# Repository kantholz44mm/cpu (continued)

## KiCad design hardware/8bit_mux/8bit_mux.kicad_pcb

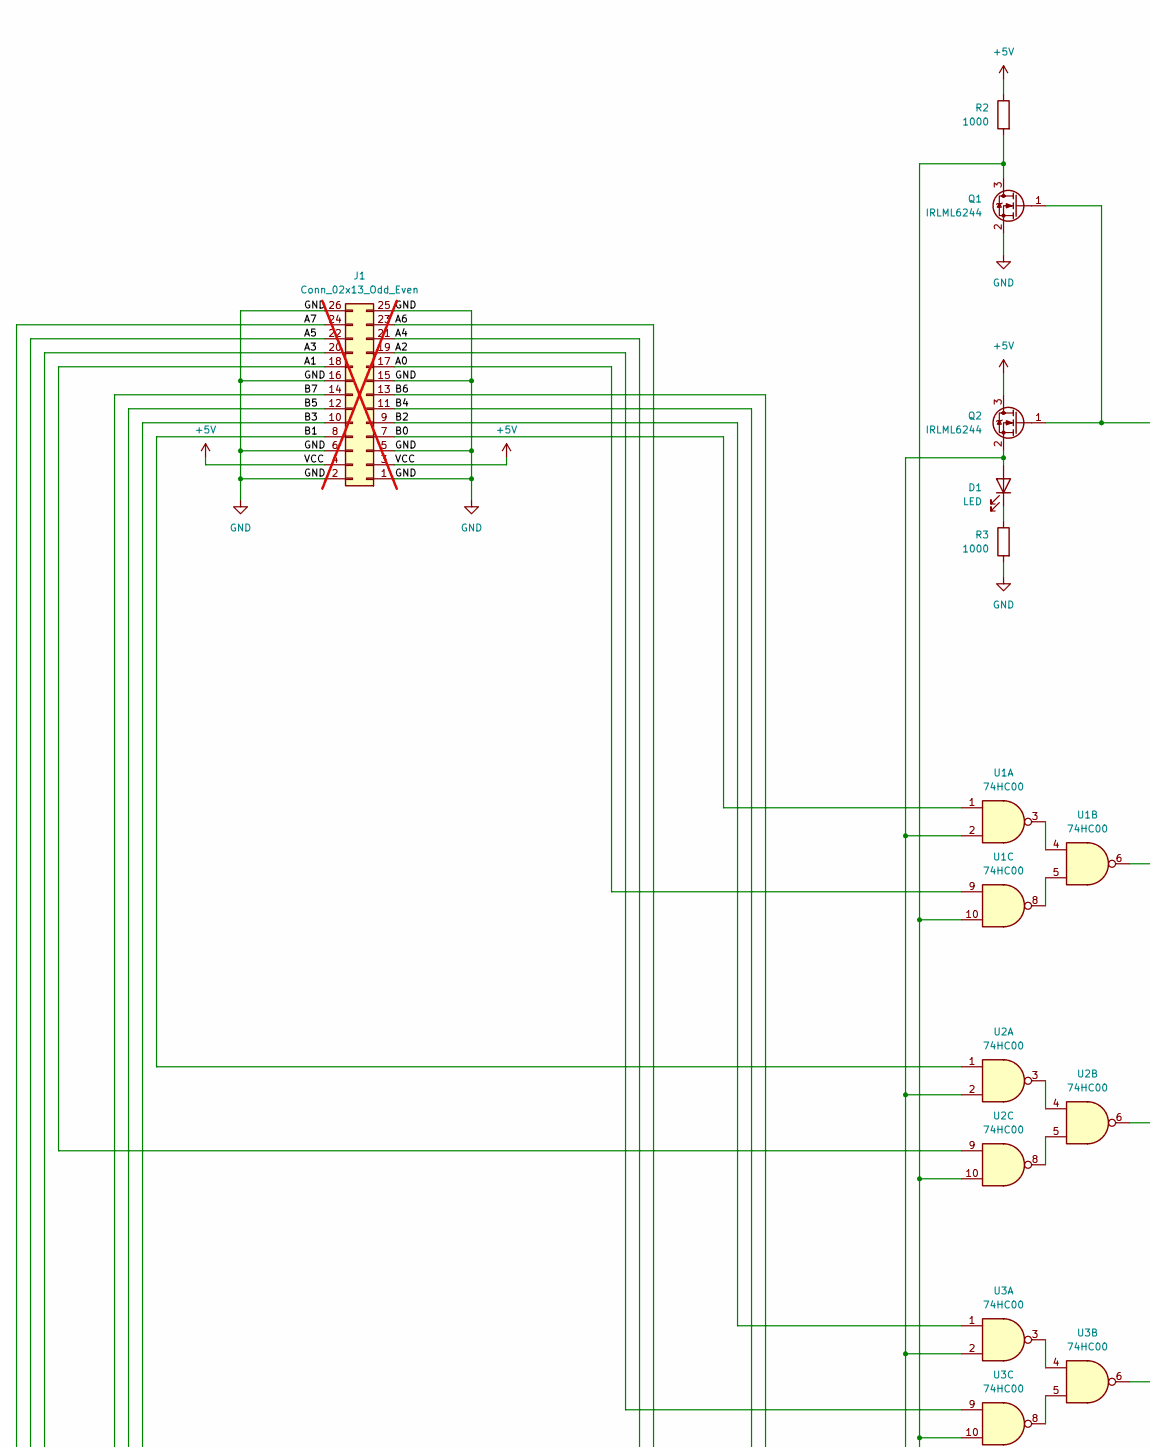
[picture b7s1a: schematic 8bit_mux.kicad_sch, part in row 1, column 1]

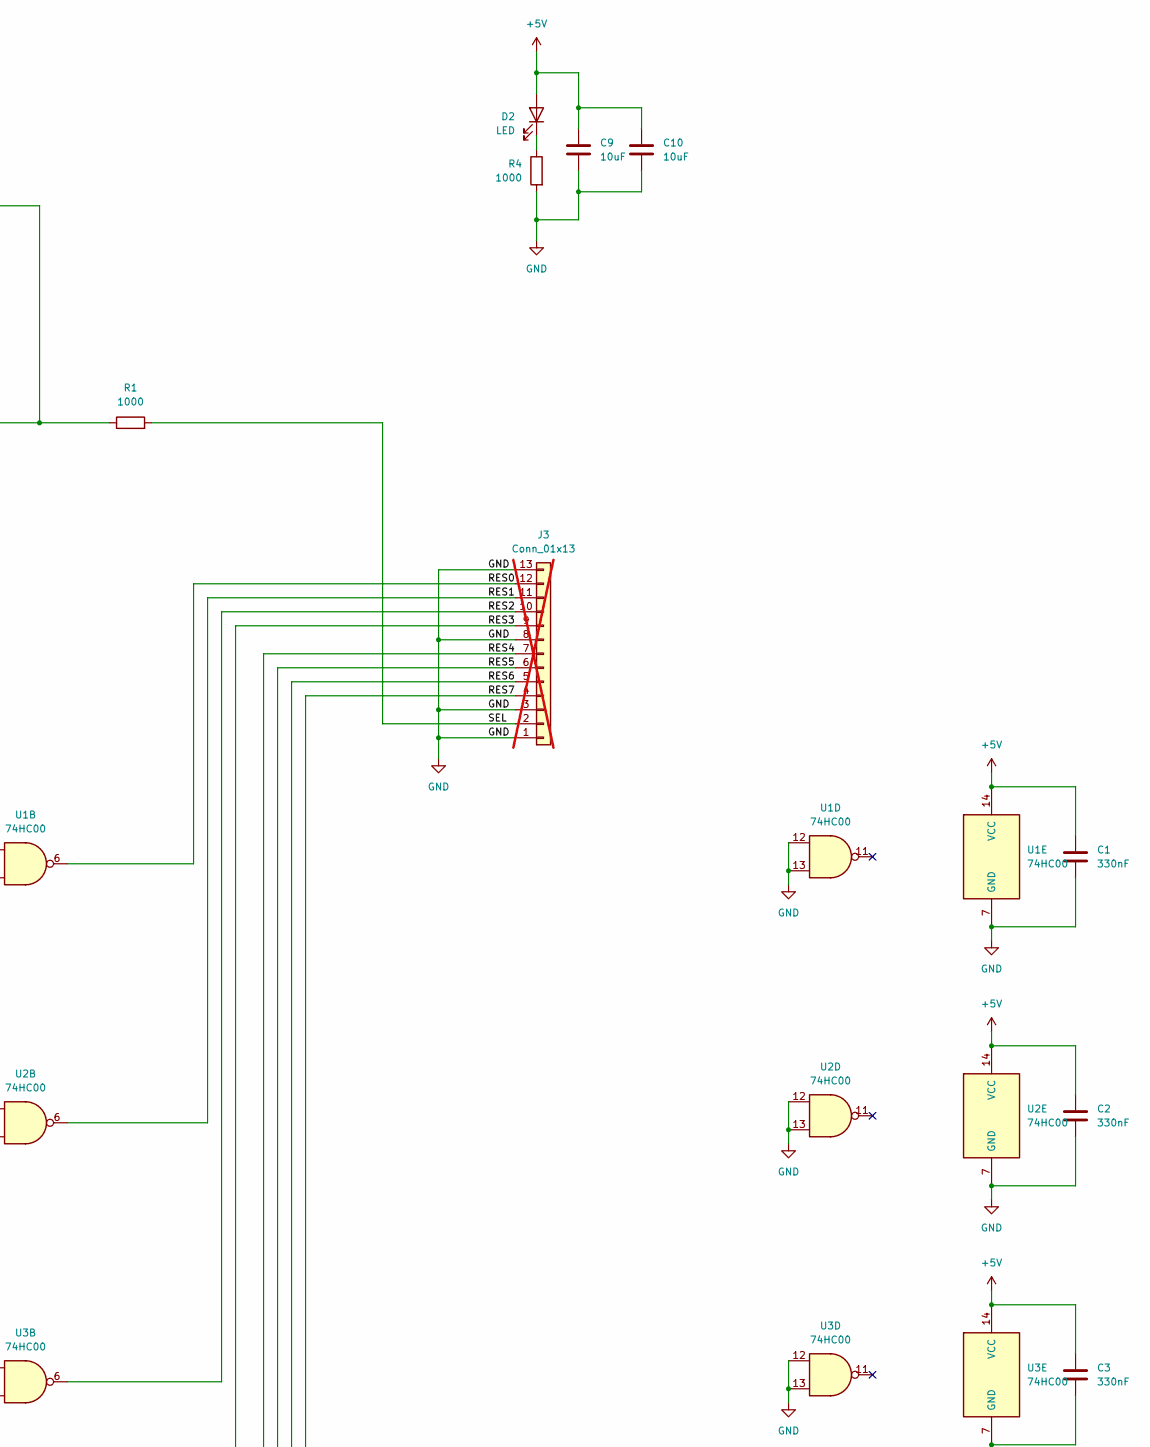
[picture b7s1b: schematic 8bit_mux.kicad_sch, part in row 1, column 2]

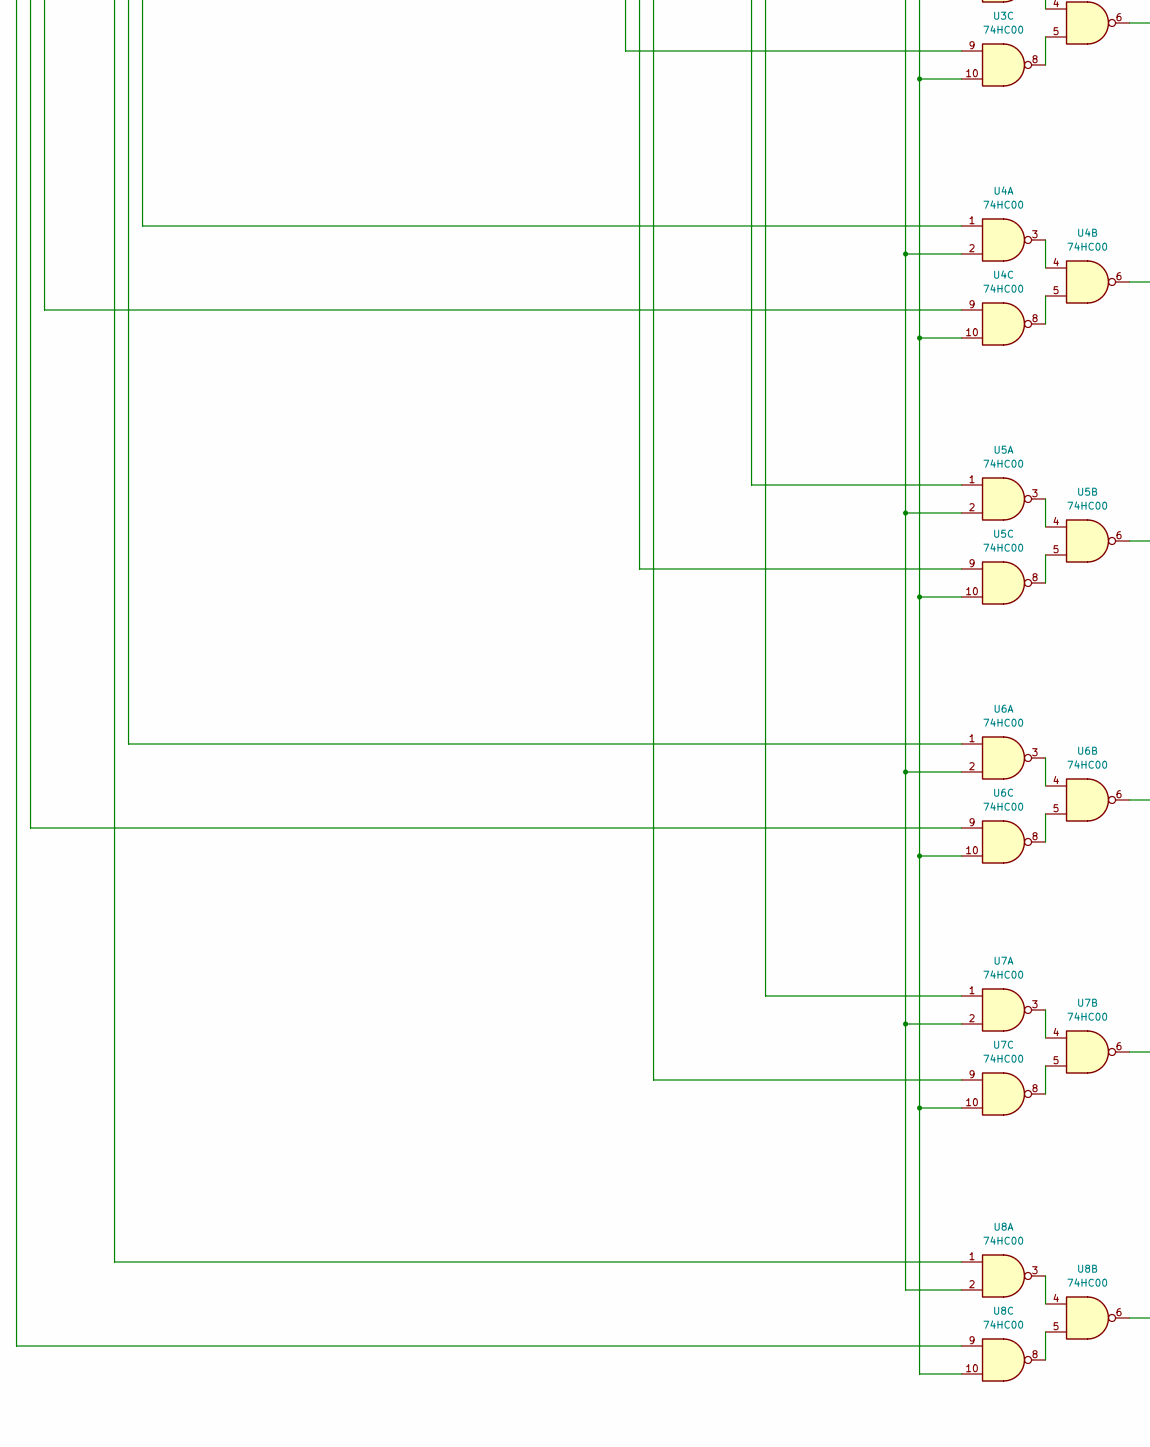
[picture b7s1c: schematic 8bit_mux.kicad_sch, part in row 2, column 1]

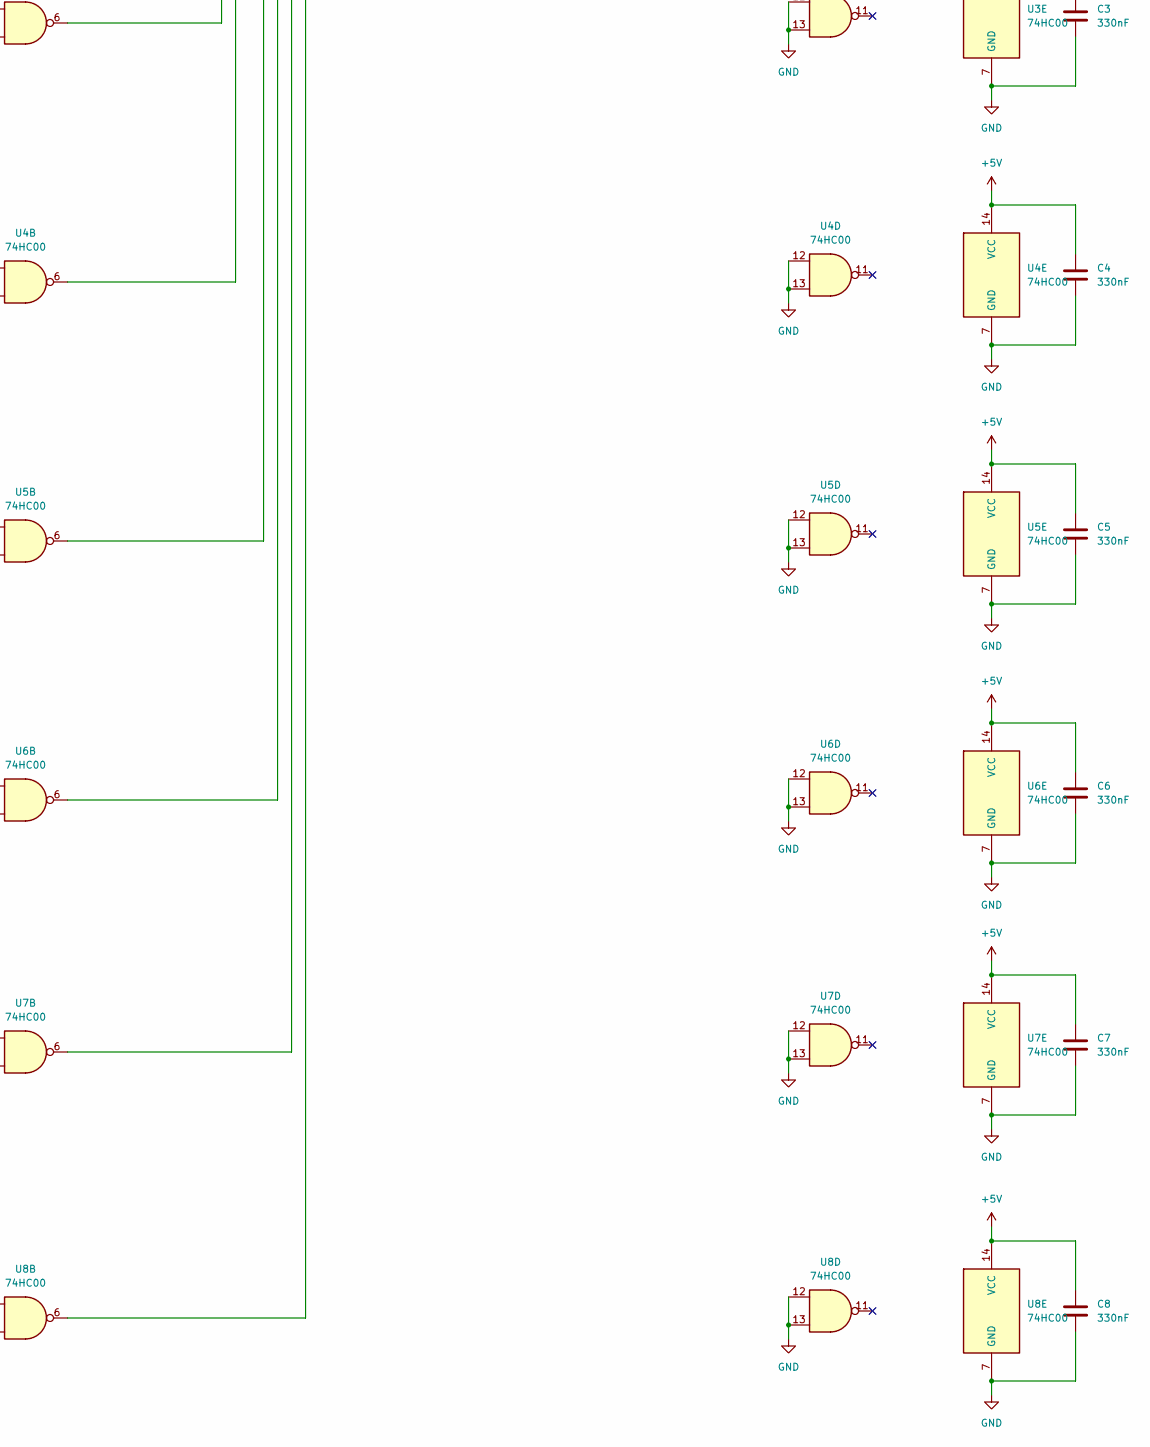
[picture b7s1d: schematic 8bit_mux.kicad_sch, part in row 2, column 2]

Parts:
C1, C2, C3, C4, C5, C6, C7, C8: 330nF; C_0603_1608Metric_Pad1.08x0.95mm_HandSolder; LCSC C2918485
C9, C10: 10uF; C_0603_1608Metric_Pad1.08x0.95mm_HandSolder; LCSC C2909630
D1, D2: LED; LED_0603_1608Metric_Pad1.05x0.95mm_HandSolder; LCSC C84267
J1: Conn_02x13_Odd_Even; PinHeader_2x13_P2.54mm_Vertical; not fitted
J3: Conn_01x13; PinHeader_1x13_P2.54mm_Vertical; not fitted
Q1, Q2: IRLML6244; SOT-23-3; LCSC C5123965
R1, R2, R3, R4: 1000; R_0603_1608Metric_Pad0.98x0.95mm_HandSolder; LCSC C21190
U1, U2, U3, U4, U5, U6, U7, U8: 74HC00; SOIC-14_3.9x8.7mm_P1.27mm; LCSC C5586

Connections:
+5V: C1.1, C2.1, C3.1, C4.1, C5.1, C6.1, C7.1, C8.1, C9.1, C10.1, D2.2 (A), J1.3, J1.4, Q2.3 (D), R2.1, U1.14 (VCC), U2.14 (VCC), U3.14 (VCC), U4.14 (VCC), U5.14 (VCC), U6.14 (VCC), U7.14 (VCC), U8.14 (VCC)
/A0: J1.17, U1.9
/A1: J1.18, U2.9
/A2: J1.19, U3.9
/A3: J1.20, U4.9
/A4: J1.21, U5.9
/A5: J1.22, U6.9
/A6: J1.23, U7.9
/A7: J1.24, U8.9
/B0: J1.7, U1.1
/B1: J1.8, U2.1
/B2: J1.9, U3.1
/B3: J1.10, U4.1
/B4: J1.11, U5.1
/B5: J1.12, U6.1
/B6: J1.13, U7.1
/B7: J1.14, U8.1
/RES0: J3.12, U1.6
/RES1: J3.11, U2.6
/RES2: J3.10, U3.6
/RES3: J3.9, U4.6
/RES4: J3.7, U5.6
/RES5: J3.6, U6.6
/RES6: J3.5, U7.6
/RES7: J3.4, U8.6
/SEL: J3.2, R1.2
GND: C1.2, C2.2, C3.2, C4.2, C5.2, C6.2, C7.2, C8.2, C9.2, C10.2, J1.1, J1.2, J1.5, J1.6, J1.15, J1.16, J1.25, J1.26, J3.1, J3.3, J3.8, J3.13, Q1.2 (S), R3.2, R4.2, U1.7 (GND), U1.12, U1.13, U2.7 (GND), U2.12, U2.13, U3.7 (GND), U3.12, U3.13, U4.7 (GND), U4.12, U4.13, U5.7 (GND), U5.12, U5.13, U6.7 (GND), U6.12, U6.13, U7.7 (GND), U7.12, U7.13, U8.7 (GND), U8.12, U8.13
unnamed: D1.2 (A), Q2.2 (S), U1.2, U2.2, U3.2, U4.2, U5.2, U6.2, U7.2, U8.2
unnamed: D1.1 (K), R3.1
unnamed: D2.1 (K), R4.1
unnamed: Q1.3 (D), R2.2, U1.10, U2.10, U3.10, U4.10, U5.10, U6.10, U7.10, U8.10
unnamed: Q1.1 (G), Q2.1 (G), R1.1
unnamed: U1.3, U1.4
unnamed: U1.5, U1.8
unnamed: U2.3, U2.4
unnamed: U2.5, U2.8
unnamed: U3.3, U3.4
unnamed: U3.5, U3.8
unnamed: U4.3, U4.4
unnamed: U4.5, U4.8
unnamed: U5.3, U5.4
unnamed: U5.5, U5.8
unnamed: U6.3, U6.4
unnamed: U6.5, U6.8
unnamed: U7.3, U7.4
unnamed: U7.5, U7.8
unnamed: U8.3, U8.4
unnamed: U8.5, U8.8

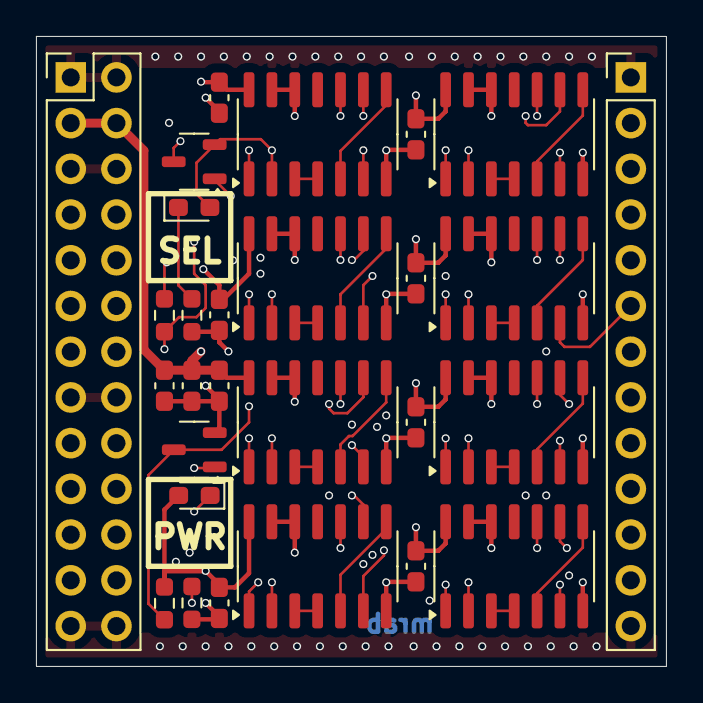
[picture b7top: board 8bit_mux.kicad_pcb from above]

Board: 4 copper layers, 35.0 x 35.0 mm, 28 parts (0 on the bottom side), 48 nets.

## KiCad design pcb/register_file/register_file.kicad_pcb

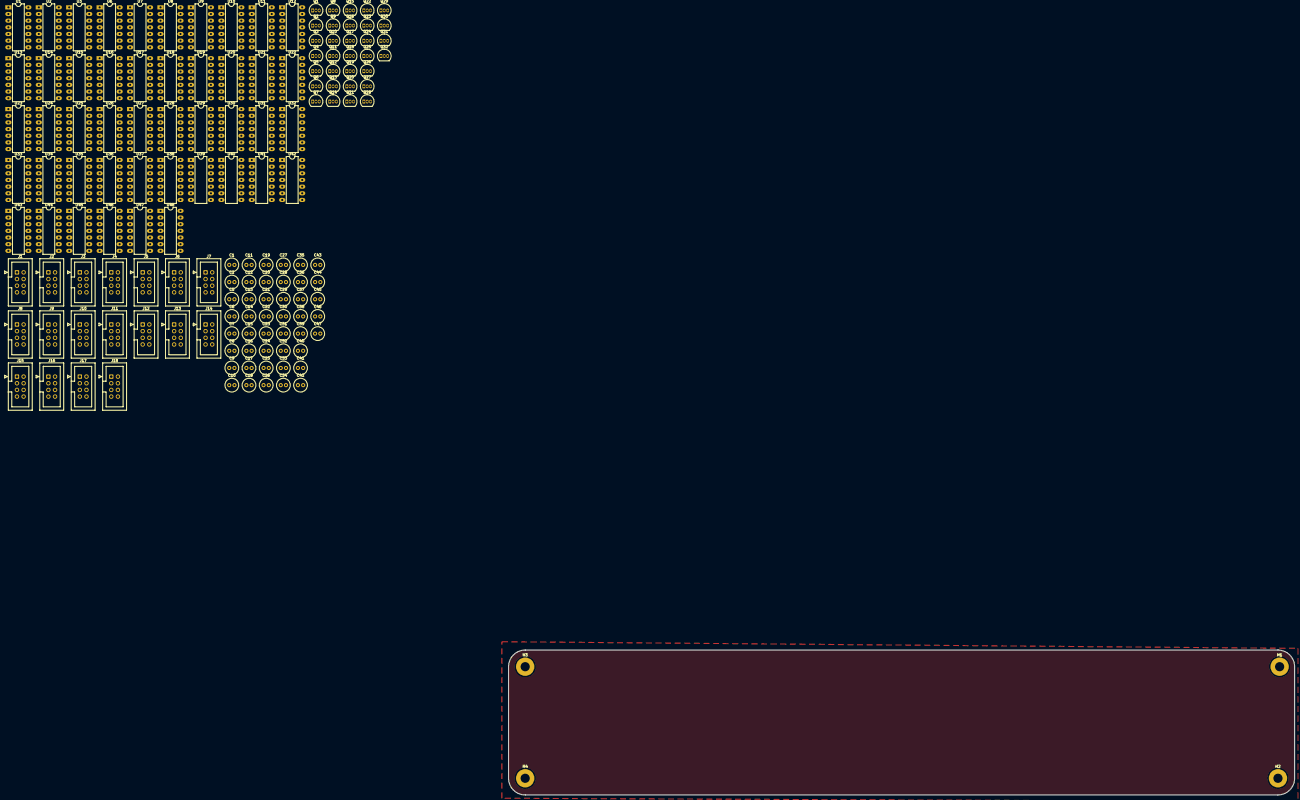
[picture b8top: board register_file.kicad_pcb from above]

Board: 2 copper layers, 299.7 x 55.2 mm, 145 parts (0 on the bottom side), 249 nets, no tracks yet.

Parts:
C1, C2, C5, C6, C7, C8, C9, C10, C11, C12, C13, C14, C15, C16, C17, C18, C19, C20, C21, C22, C23, C24, C25, C26, C27, C28, C29, C30, C31, C32, C33, C34, C35, C36, C37, C38, C39, C40, C41, C42, C43, C44, C45, C46, C47: C_Small; C_Radial_D5.0mm_H11.0mm_P2.00mm
H1, H2, H3, H4: MountingHole_Pad; MountingHole_3.5mm_Pad
J1: READ1; IDC-Header_2x04_P2.54mm_Vertical
J2: READ2; IDC-Header_2x04_P2.54mm_Vertical
J3: REG0_READ; IDC-Header_2x04_P2.54mm_Vertical
J4: WRITE; IDC-Header_2x04_P2.54mm_Vertical
J5: SELECT; IDC-Header_2x04_P2.54mm_Vertical
J6: CONTROL; IDC-Header_2x04_P2.54mm_Vertical
J7: REG0_CONTROL; IDC-Header_2x04_P2.54mm_Vertical
J8: REG1_CONTROL; IDC-Header_2x04_P2.54mm_Vertical
J9: REG2_CONTROL; IDC-Header_2x04_P2.54mm_Vertical
J10: REG3_CONTROL; IDC-Header_2x04_P2.54mm_Vertical
J11: REG0_WRITE; IDC-Header_2x04_P2.54mm_Vertical
J12: REG1_WRITE; IDC-Header_2x04_P2.54mm_Vertical
J13: REG2_WRITE; IDC-Header_2x04_P2.54mm_Vertical
J14: REG3_WRITE; IDC-Header_2x04_P2.54mm_Vertical
J15: REG1_READ; IDC-Header_2x04_P2.54mm_Vertical
J16: REG2_READ; IDC-Header_2x04_P2.54mm_Vertical
J17: REG3_READ; IDC-Header_2x04_P2.54mm_Vertical
J18: READP; IDC-Header_2x04_P2.54mm_Vertical
Q1, Q4, Q6, Q8, Q10, Q12, Q14, Q16, Q18, Q20, Q22, Q24, Q26, Q28, Q30, Q32: 2N7000; TO-92_Inline
Q2, Q3, Q5, Q7, Q9, Q11, Q13, Q15, Q17, Q19, Q21, Q23, Q25, Q27, Q29, Q31: BS250; TO-92_Inline
U1, U2, U3, U6, U7, U8, U9, U10, U11, U12, U13, U14, U15, U16, U17, U18, U19, U20, U21, U22, U23, U24, U25, U26, U27, U28, U29, U30, U31, U32, U33, U34, U35, U36, U37, U38, U39, U40, U41, U42, U43, U44, U45, U46, U47, U48: 74HC00; DIP-14_W7.62mm_LongPads

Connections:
+5V: C1.1, C2.1, C5.1, C6.1, C7.1, C8.1, C9.1, C10.1, C11.1, C12.1, C13.1, C14.1, C15.1, C16.1, C17.1, C18.1, C19.1, C20.1, C21.1, C22.1, C23.1, C24.1, C25.1, C26.1, C27.1, C28.1, C29.1, C30.1, C31.1, C32.1, C33.1, C34.1, C35.1, C36.1, C37.1, C38.1, C39.1, C40.1, C41.1, C42.1, C43.1, C44.1, C45.1, C46.1, C47.1, J6.7, J6.8, J7.7, J7.8, J8.7, J8.8, J9.7, J9.8, J10.7, J10.8, Q2.1 (D), Q3.1 (D), Q5.1 (D), Q7.1 (D), Q9.1 (D), Q11.1 (D), Q13.1 (D), Q15.1 (D), Q17.1 (D), Q19.1 (D), Q21.1 (D), Q23.1 (D), Q25.1 (D), Q27.1 (D), Q29.1 (D), Q31.1 (D), U1.14 (VCC), U2.14 (VCC), U3.14 (VCC), U6.14 (VCC), U7.14 (VCC), U8.14 (VCC), U9.14 (VCC), U10.14 (VCC), U11.14 (VCC), U12.14 (VCC), U13.14 (VCC), U14.14 (VCC), U15.14 (VCC), U16.14 (VCC), U17.14 (VCC), U18.14 (VCC), U19.14 (VCC), U20.14 (VCC), U21.14 (VCC), U22.14 (VCC), U23.14 (VCC), U24.14 (VCC), U25.14 (VCC), U26.14 (VCC), U27.14 (VCC), U28.14 (VCC), U29.14 (VCC), U30.14 (VCC), U31.14 (VCC), U32.14 (VCC), U33.14 (VCC), U34.14 (VCC), U35.14 (VCC), U36.14 (VCC), U37.14 (VCC), U38.14 (VCC), U39.14 (VCC), U40.14 (VCC), U41.14 (VCC), U42.14 (VCC), U43.14 (VCC), U44.14 (VCC), U45.14 (VCC), U46.14 (VCC), U47.14 (VCC), U48.14 (VCC)
GND: C1.2, C2.2, C5.2, C6.2, C7.2, C8.2, C9.2, C10.2, C11.2, C12.2, C13.2, C14.2, C15.2, C16.2, C17.2, C18.2, C19.2, C20.2, C21.2, C22.2, C23.2, C24.2, C25.2, C26.2, C27.2, C28.2, C29.2, C30.2, C31.2, C32.2, C33.2, C34.2, C35.2, C36.2, C37.2, C38.2, C39.2, C40.2, C41.2, C42.2, C43.2, C44.2, C45.2, C46.2, C47.2, H1.1, H2.1, H3.1, H4.1, J5.3, J5.6, J6.4, J6.5, J6.6, J7.4, J7.5, J7.6, J8.4, J8.5, J8.6, J9.4, J9.5, J9.6, J10.4, J10.5, J10.6, Q1.1 (S), Q4.1 (S), Q6.1 (S), Q8.1 (S), Q10.1 (S), Q12.1 (S), Q14.1 (S), Q16.1 (S), Q18.1 (S), Q20.1 (S), Q22.1 (S), Q24.1 (S), Q26.1 (S), Q28.1 (S), Q30.1 (S), Q32.1 (S), U1.7 (GND), U2.7 (GND), U3.7 (GND), U6.7 (GND), U7.7 (GND), U8.7 (GND), U9.7 (GND), U10.7 (GND), U11.7 (GND), U12.7 (GND), U13.7 (GND), U14.7 (GND), U15.7 (GND), U16.7 (GND), U17.7 (GND), U18.7 (GND), U19.7 (GND), U20.7 (GND), U21.7 (GND), U22.7 (GND), U23.7 (GND), U24.7 (GND), U25.7 (GND), U26.7 (GND), U27.7 (GND), U28.7 (GND), U29.7 (GND), U30.7 (GND), U31.7 (GND), U32.7 (GND), U33.7 (GND), U34.7 (GND), U35.7 (GND), U36.7 (GND), U37.7 (GND), U38.7 (GND), U39.7 (GND), U40.7 (GND), U41.7 (GND), U42.7 (GND), U43.7 (GND), U44.7 (GND), U45.7 (GND), U46.7 (GND), U47.7 (GND), U48.7 (GND)
unnamed: J1.1, U19.3
unnamed: J1.2, U19.8
unnamed: J1.3, U21.3
unnamed: J1.4, U21.8
unnamed: J1.5, U30.3
unnamed: J1.6, U30.8
unnamed: J1.7, U39.3
unnamed: J1.8, U39.8
unnamed: J2.1, U19.6
unnamed: J2.2, U19.11
unnamed: J2.3, U21.6
unnamed: J2.4, U21.11
unnamed: J2.5, U30.6
unnamed: J2.6, U30.11
unnamed: J2.7, U39.6
unnamed: J2.8, U39.11
unnamed: J3.1, U11.2, U13.2
unnamed: J3.2, U15.2, U17.2
unnamed: J3.3, U20.2, U23.2
unnamed: J3.4, U25.2, U27.2
unnamed: J3.5, U29.2, U32.2
unnamed: J3.6, U34.2, U36.2
unnamed: J3.7, U38.2, U41.2
unnamed: J3.8, U43.2, U45.2
unnamed: J4.1, U48.12, U48.13
unnamed: J4.2, U48.9, U48.10
unnamed: J4.3, U48.4, U48.5
unnamed: J4.4, U48.1, U48.2
unnamed: J4.5, U47.12, U47.13
unnamed: J4.6, U47.9, U47.10
unnamed: J4.7, U47.4, U47.5
unnamed: J4.8, U47.1, U47.2
unnamed: J5.1, U6.1, U6.2, U8.2, U8.10
unnamed: J5.2, U6.4, U6.5, U7.9, U8.9
unnamed: J5.4, U2.10, U2.13, U3.9, U3.10
unnamed: J5.5, U2.4, U2.12, U3.12, U3.13
unnamed: J5.7, U1.10, U1.13, U3.1, U3.2
unnamed: J5.8, U1.4, U1.12, U3.4, U3.5
unnamed: J6.2, U9.1, U9.9, U10.1, U10.9
unnamed: J7.2, U9.6
unnamed: J8.2, U9.11
unnamed: J9.2, U10.6
unnamed: J6.1, J7.1, J8.1, J9.1, J10.1
unnamed: J10.2, U10.11
unnamed: J6.3, J7.3, J8.3, J9.3, J10.3
unnamed: J11.1, J12.1, J13.1, J14.1, Q15.3 (S), Q16.3 (D)
unnamed: J11.2, J12.2, J13.2, J14.2, Q13.3 (S), Q14.3 (D)
unnamed: J11.3, J12.3, J13.3, J14.3, Q11.3 (S), Q12.3 (D)
unnamed: J11.4, J12.4, J13.4, J14.4, Q9.3 (S), Q10.3 (D)
unnamed: J11.5, J12.5, J13.5, J14.5, Q7.3 (S), Q8.3 (D)
unnamed: J11.6, J12.6, J13.6, J14.6, Q5.3 (S), Q6.3 (D)
unnamed: J11.7, J12.7, J13.7, J14.7, Q3.3 (S), Q4.3 (D)
unnamed: J11.8, J12.8, J13.8, J14.8, Q1.3 (D), Q2.3 (S)
unnamed: J15.1, U11.5, U13.5
unnamed: J15.2, U15.5, U17.5
unnamed: J15.3, U20.5, U23.5
unnamed: J15.4, U25.5, U27.5
unnamed: J15.5, U29.5, U32.5
unnamed: J15.6, U34.5, U36.5
unnamed: J15.7, U38.5, U41.5
unnamed: J15.8, U43.5, U45.5
unnamed: J16.1, U12.2, U14.2
unnamed: J16.2, U16.2, U18.2
unnamed: J16.3, U22.2, U24.2
unnamed: J16.4, U26.2, U28.2
unnamed: J16.5, U31.2, U33.2
unnamed: J16.6, U35.2, U37.2
unnamed: J16.7, U40.2, U42.2
unnamed: J16.8, U44.2, U46.2
unnamed: J17.1, J18.1, U12.5, U14.5
unnamed: J17.2, J18.2, U16.5, U18.5
unnamed: J17.3, J18.3, U22.5, U24.5
unnamed: J17.4, J18.4, U26.5, U28.5
unnamed: J17.5, J18.5, U31.5, U33.5
unnamed: J17.6, J18.6, U35.5, U37.5
unnamed: J17.7, J18.7, U40.5, U42.5
unnamed: J17.8, J18.8, U44.5, U46.5
unnamed: Q1.2 (G), Q2.2 (G), U47.3
unnamed: Q3.2 (G), Q4.2 (G), U47.6
unnamed: Q5.2 (G), Q6.2 (G), U47.8
unnamed: Q7.2 (G), Q8.2 (G), U47.11
unnamed: Q9.2 (G), Q10.2 (G), U48.3
unnamed: Q11.2 (G), Q12.2 (G), U48.6
unnamed: Q13.2 (G), Q14.2 (G), U48.8
unnamed: Q15.2 (G), Q16.2 (G), U48.11
unnamed: Q17.2 (G), Q18.2 (G), U1.3
unnamed: Q17.3 (S), Q18.3 (D), U11.1, U15.1, U20.1, U25.1, U29.1, U34.1, U38.1, U43.1
unnamed: Q19.2 (G), Q20.2 (G), U1.6
unnamed: Q19.3 (S), Q20.3 (D), U11.4, U15.4, U20.4, U25.4, U29.4, U34.4, U38.4, U43.4
unnamed: Q21.2 (G), Q22.2 (G), U1.8
unnamed: Q21.3 (S), Q22.3 (D), U12.1, U16.1, U22.1, U26.1, U31.1, U35.1, U40.1, U44.1
unnamed: Q23.2 (G), Q24.2 (G), U1.11
unnamed: Q23.3 (S), Q24.3 (D), U12.4, U16.4, U22.4, U26.4, U31.4, U35.4, U40.4, U44.4
unnamed: Q25.2 (G), Q26.2 (G), U2.3
unnamed: Q25.3 (S), Q26.3 (D), U14.4, U18.4, U24.4, U28.4, U33.4, U37.4, U42.4, U46.4
unnamed: Q27.2 (G), Q28.2 (G), U2.6
unnamed: Q27.3 (S), Q28.3 (D), U14.1, U18.1, U24.1, U28.1, U33.1, U37.1, U42.1, U46.1
unnamed: Q29.2 (G), Q30.2 (G), U2.8
unnamed: Q29.3 (S), Q30.3 (D), U13.4, U17.4, U23.4, U27.4, U32.4, U36.4, U41.4, U45.4
unnamed: Q31.2 (G), Q32.2 (G), U2.11
unnamed: Q31.3 (S), Q32.3 (D), U13.1, U17.1, U23.1, U27.1, U32.1, U36.1, U41.1, U45.1
unnamed: U1.1, U1.9, U3.6
unnamed: U1.2, U1.5, U3.3
unnamed: U2.1, U2.9, U3.11
unnamed: U2.2, U2.5, U3.8
unnamed: U6.3, U7.2, U7.10
unnamed: U6.6, U7.1, U8.1
unnamed: U7.3, U7.4, U7.5
unnamed: U7.6, U9.2
unnamed: U7.11, U9.10
unnamed: U7.8, U7.12, U7.13
unnamed: U8.3, U8.4, U8.5
unnamed: U8.8, U8.12, U8.13
unnamed: U9.3, U9.4, U9.5
unnamed: U9.8, U9.12, U9.13
unnamed: U8.6, U10.2
unnamed: U10.3, U10.4, U10.5
unnamed: U8.11, U10.10
unnamed: U10.8, U10.12, U10.13
unnamed: U11.3, U11.9
unnamed: U11.6, U11.10
unnamed: U11.11, U19.1
unnamed: U11.8, U11.12, U11.13
unnamed: U12.3, U12.9
unnamed: U12.6, U12.10
unnamed: U12.11, U19.2
unnamed: U12.8, U12.12, U12.13
unnamed: U13.3, U13.9
unnamed: U13.6, U13.10
unnamed: U13.11, U19.4
unnamed: U13.8, U13.12, U13.13
unnamed: U14.3, U14.9
unnamed: U14.6, U14.10
unnamed: U14.11, U19.5
unnamed: U14.8, U14.12, U14.13
unnamed: U15.3, U15.9
unnamed: U15.6, U15.10
unnamed: U15.11, U19.9
unnamed: U15.8, U15.12, U15.13
unnamed: U16.3, U16.9
unnamed: U16.6, U16.10
unnamed: U16.11, U19.10
unnamed: U16.8, U16.12, U16.13
unnamed: U17.3, U17.9
unnamed: U17.6, U17.10
unnamed: U17.11, U19.12
unnamed: U17.8, U17.12, U17.13
unnamed: U18.3, U18.9
unnamed: U18.6, U18.10
unnamed: U18.11, U19.13
unnamed: U18.8, U18.12, U18.13
unnamed: U20.3, U20.9
unnamed: U20.6, U20.10
unnamed: U20.11, U21.1
unnamed: U20.8, U20.12, U20.13
unnamed: U21.2, U22.11
unnamed: U21.4, U23.11
unnamed: U21.5, U24.11
unnamed: U21.9, U25.11
unnamed: U21.10, U26.11
unnamed: U21.12, U27.11
unnamed: U21.13, U28.11
unnamed: U22.3, U22.9
unnamed: U22.6, U22.10
unnamed: U22.8, U22.12, U22.13
unnamed: U23.3, U23.9
unnamed: U23.6, U23.10
unnamed: U23.8, U23.12, U23.13
unnamed: U24.3, U24.9
unnamed: U24.6, U24.10
unnamed: U24.8, U24.12, U24.13
unnamed: U25.3, U25.9
unnamed: U25.6, U25.10
unnamed: U25.8, U25.12, U25.13
unnamed: U26.3, U26.9
unnamed: U26.6, U26.10
unnamed: U26.8, U26.12, U26.13
unnamed: U27.3, U27.9
unnamed: U27.6, U27.10
unnamed: U27.8, U27.12, U27.13
unnamed: U28.3, U28.9
unnamed: U28.6, U28.10
unnamed: U28.8, U28.12, U28.13
unnamed: U29.3, U29.9
unnamed: U29.6, U29.10
unnamed: U29.11, U30.1
unnamed: U29.8, U29.12, U29.13
unnamed: U30.2, U31.11
unnamed: U30.4, U32.11
unnamed: U30.5, U33.11
unnamed: U30.9, U34.11
unnamed: U30.10, U35.11
unnamed: U30.12, U36.11
unnamed: U30.13, U37.11
unnamed: U31.3, U31.9
unnamed: U31.6, U31.10
unnamed: U31.8, U31.12, U31.13
unnamed: U32.3, U32.9
unnamed: U32.6, U32.10
unnamed: U32.8, U32.12, U32.13
unnamed: U33.3, U33.9
unnamed: U33.6, U33.10
unnamed: U33.8, U33.12, U33.13
unnamed: U34.3, U34.9
unnamed: U34.6, U34.10
unnamed: U34.8, U34.12, U34.13
unnamed: U35.3, U35.9
unnamed: U35.6, U35.10
unnamed: U35.8, U35.12, U35.13
unnamed: U36.3, U36.9
unnamed: U36.6, U36.10
unnamed: U36.8, U36.12, U36.13
unnamed: U37.3, U37.9
unnamed: U37.6, U37.10
unnamed: U37.8, U37.12, U37.13
unnamed: U38.3, U38.9
unnamed: U38.6, U38.10
unnamed: U38.11, U39.1
unnamed: U38.8, U38.12, U38.13
unnamed: U39.2, U40.11
unnamed: U39.4, U41.11
unnamed: U39.5, U42.11
unnamed: U39.9, U43.11
unnamed: U39.10, U44.11
unnamed: U39.12, U45.11
unnamed: U39.13, U46.11
unnamed: U40.3, U40.9
unnamed: U40.6, U40.10
unnamed: U40.8, U40.12, U40.13
unnamed: U41.3, U41.9
unnamed: U41.6, U41.10
unnamed: U41.8, U41.12, U41.13
unnamed: U42.3, U42.9
unnamed: U42.6, U42.10
unnamed: U42.8, U42.12, U42.13
unnamed: U43.3, U43.9
unnamed: U43.6, U43.10
unnamed: U43.8, U43.12, U43.13
unnamed: U44.3, U44.9
unnamed: U44.6, U44.10
unnamed: U44.8, U44.12, U44.13
unnamed: U45.3, U45.9
unnamed: U45.6, U45.10
unnamed: U45.8, U45.12, U45.13
unnamed: U46.3, U46.9
unnamed: U46.6, U46.10
unnamed: U46.8, U46.12, U46.13

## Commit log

2023-11-19 Initial state
2023-11-20 started work on assembler
2023-11-20 sim standing, MWI, ADD working
2023-11-20 assembler: encoding done, mostly untested as of yet
2023-11-20 added test case
2023-11-20 added .gitignore
2023-11-20 removed build files
2023-11-20 moved gitignore and cleaned up
2023-11-21 parsing tokens
2023-11-21 parsing first couple instructions
2023-11-21 all mnemonics can be assembled
2023-11-23 compiling and executing the first program
2023-11-25 reverted to 4 register core
2023-11-25 changed to async SRAM, added IO bus
2023-11-25 added example GPIO output, working fibonacci program
2023-11-25 removed example gpio setup
2023-11-26 16 bit fibonacci working
2023-11-30 Asynchronous reset lines for all registers
2023-11-30 added logic for halt/continue and HCF instruction
2023-11-30 Added Async CLR to flags register
2023-11-30 consolidated
2023-12-21 added kicad files for register
2024-01-16 register file
2024-04-20 separate page register
2024-04-21 label support for assembler
2024-04-21 comma = whitespace in assembler
2024-04-24 Fixed B Operand flag for ALUI and CMPI
2024-04-24 ALUF and ALUFI
2024-04-24 fixed Memory clocking
2024-10-23 clean up repo
2024-10-24 added project documentation documents
2024-11-07 feedback
2024-11-07 updated ISA spec
2024-11-07 added framework for thesis
2024-11-07 added interconnect & layout diagram
2024-11-23 Removed JZ and JNZ, made BZ and BNZ take RO2 as decider
2024-11-24 added register pcb
2024-11-24 started CPU emulator software
2024-11-24 added emulator tick logic, only ALU missing
2024-11-25 added ALU from combinatorial emulation
2024-11-25 fixed order of ALU flags
2024-11-26 fixed overflow flag checking in fib example
2024-11-26 added simple graphics test, drawing rectangle
2024-11-26 fixed unused imports, added 'current address' ($) to assembler
2024-11-26 added example for function calling
2024-12-04 redesigned register PCB with SMD components
2024-12-05 generated production files, including BOM and POS
2024-12-05 removed redundant mux from ALU
2024-12-05 added section on ISA design
2024-12-08 redesigned register using SMD components
2024-12-10 Added schematic for alu sub/add module
2024-12-11 layout done for alu add sub (missing test points)
2024-12-11 finalized PCB for ordering (LCSC parts, silkscreen, etc)
2025-01-19 worked some on the thesis, started next alu module
2025-01-19 WIP, moved all control signals into OPROM, modified assembler as such
2025-01-19 added johnson 4 bit counter for synchronisation (fixes branching)
2025-01-21 finished design of ALU binary logic module
2025-01-21 added initial schematic for ALU shifter module
2025-01-22 added section on commissioning
2025-01-22 added LED indicators for ALU shift module
2025-01-23 added section on timing, restructured
2025-01-25 added 8 bit mux pcb, started work on ALU shifter
2025-01-28 finished ALU Shift module, all ALU modules completed
2025-01-31 added math expression evaluator to assembler, updated emulator
2025-02-04 started work on ALU motherboard
2025-02-04 fixed schematic of ALU motherboard
2025-02-05 finished schematic and draft of ALU motherboard
2025-02-09 feedback to ALU motherboard PCB
2025-02-09 more ALU motherboard feedback
2025-02-11 reverted changes to alu_shift
2025-02-11 added PWR indicator to alu_shift
2025-02-12 fixed mux include
2025-02-12 ALU shifter, bitops and motherboard as ordered
2025-02-17 removed regex dependency from lexer
2025-02-17 reduced dependencies
2025-03-13 updated boolean logic section
2025-03-14 updated section on boolean logic and cpu and timing
2025-03-16 added sections on design, reworked isa section
2025-03-19 added section on software
2025-03-19 finished PCB assembly layout
2025-03-20 started section on software emulator
2025-03-20 added single-pcb ALU V2
2025-03-23 WIP progress on ALU V2 pcb
2025-03-24 more WIP work on ALU V2
2025-03-25 further WIP on ALU V2 pcb
2025-03-25 ALU V2 done?
2025-03-26 small fixes in ALU V2, started work on register fabric, schematic done (?)
2025-04-01 fixed ALU order of Op bits, finished register fabric schematic
2025-04-01 started work on register fabric PCB layout, grouped LEDs
2025-04-02 finished Rev A of register fabric pcb
2025-04-03 added fiducials and markers to ALU, started on register fabric
2025-04-04 added fiducials to register fabric REV A
2025-04-06 small fixes on register fabric
2025-04-08 did a good chunk of IO PCB schematic
2025-04-15 IO PCB schematic REV A done?
2025-04-16 added folder for documentation organisation
2025-04-16 Added sections on microcode and busses
2025-04-17 added section on microcode
2025-04-19 almost done with placement for IO board
2025-04-21 finished IO PCB placement
2025-04-21 large chunk of IO PCB routing is done
2025-04-22 more work on IO PCB routing
2025-04-22 added section on PCB
2025-04-22 minor work on ISA text
2025-04-22 io pcb done. :)
2025-04-23 silkscreen done for IO PCB
2025-04-25 added Traco DCDC, not hooked up yet
2025-04-27 all PCBs passing all CRC & vibe checks
2025-04-27 as ordered
2025-05-05 refactored section on memory
2025-05-06 added DIO for datapath, added section on addressing modes
2025-05-09 added section on opcodes
2025-05-09 added expressions from NAND
2025-05-12 added large parts of modularisation in logical design section
2025-05-13 finished module description, started on interconnection
2025-05-14 completed interconnect section, added multiplexers to modularisation section
2025-05-14 finished (?) section on simulation
2025-05-15 added section on emulator
2025-05-19 finished list of components in hardware section
2025-05-27 added pie chart of gate distribution and section on modules
2025-05-28 wrote some stuff in schematic and simulation
2025-05-29 wrote a lot about schematics and pcb, almost done.
2025-05-30 added loads of text to schematic, pcb, outro and abstract
2025-05-30 content is done. no more. just polish left
2025-05-31 fin?
2026-04-16 Added License
